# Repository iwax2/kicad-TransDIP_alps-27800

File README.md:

# kicad-TransDIP_alps-27800

Translate 2-axis Joystick ALPS RKJXV1224005 as DIP package in 2-axis Joystick #27800

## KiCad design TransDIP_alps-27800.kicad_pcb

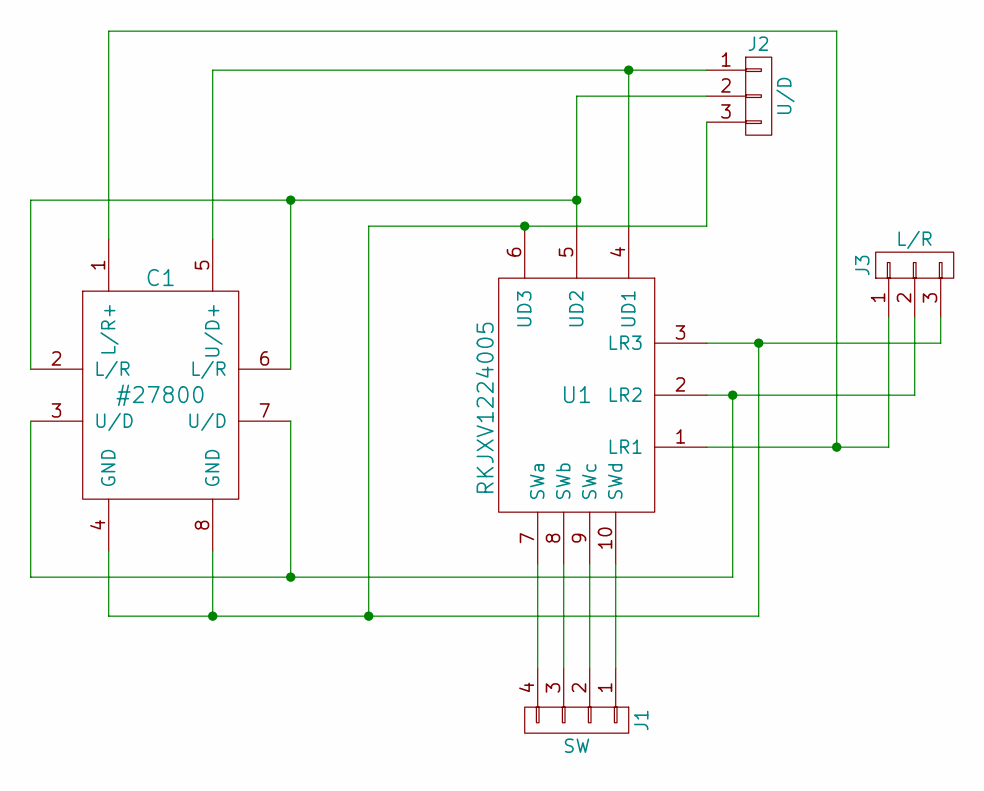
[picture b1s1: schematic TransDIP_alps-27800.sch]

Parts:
C1: #27800; 27800
J1: SW; Pin_Header_Straight_1x04_Pitch2.54mm
J2: U/D; Pin_Header_Straight_1x03_Pitch2.54mm
J3: L/R; Pin_Header_Straight_1x03_Pitch2.54mm
U1: RKJXV1224005

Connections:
unnamed: C1.1 (L/R+), J3.1, U1.1 (LR1)
unnamed: C1.2 (L/R), C1.6 (L/R), J2.2, U1.5 (UD2)
unnamed: C1.3 (U/D), C1.7 (U/D), J3.2, U1.2 (LR2)
unnamed: C1.4 (GND), C1.8 (GND), J2.3, J3.3, U1.3 (LR3), U1.6 (UD3)
unnamed: C1.5 (U/D+), J2.1, U1.4 (UD1)
unnamed: J1.1, U1.10 (SWd)
unnamed: J1.2, U1.9 (SWc)
unnamed: J1.3, U1.8 (SWb)
unnamed: J1.4, U1.7 (SWa)

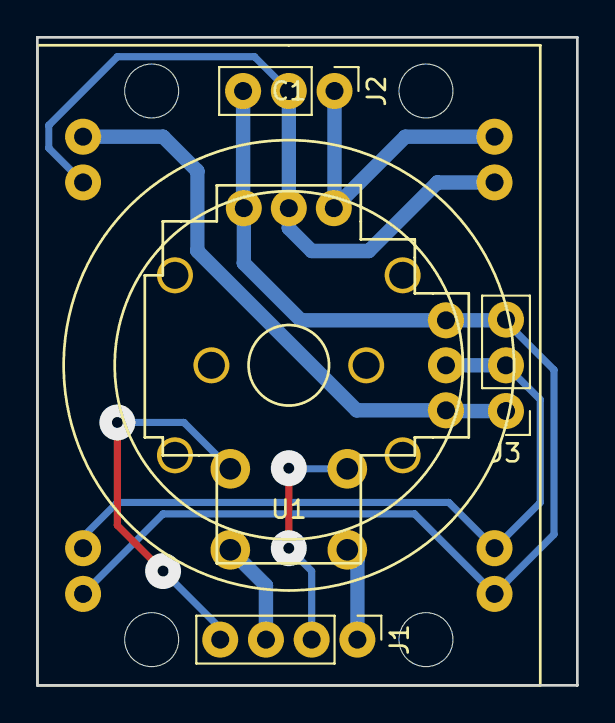
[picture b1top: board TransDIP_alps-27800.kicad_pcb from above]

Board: 2 copper layers, 30.0 x 36.0 mm, 5 parts (0 on the bottom side), 9 nets.
